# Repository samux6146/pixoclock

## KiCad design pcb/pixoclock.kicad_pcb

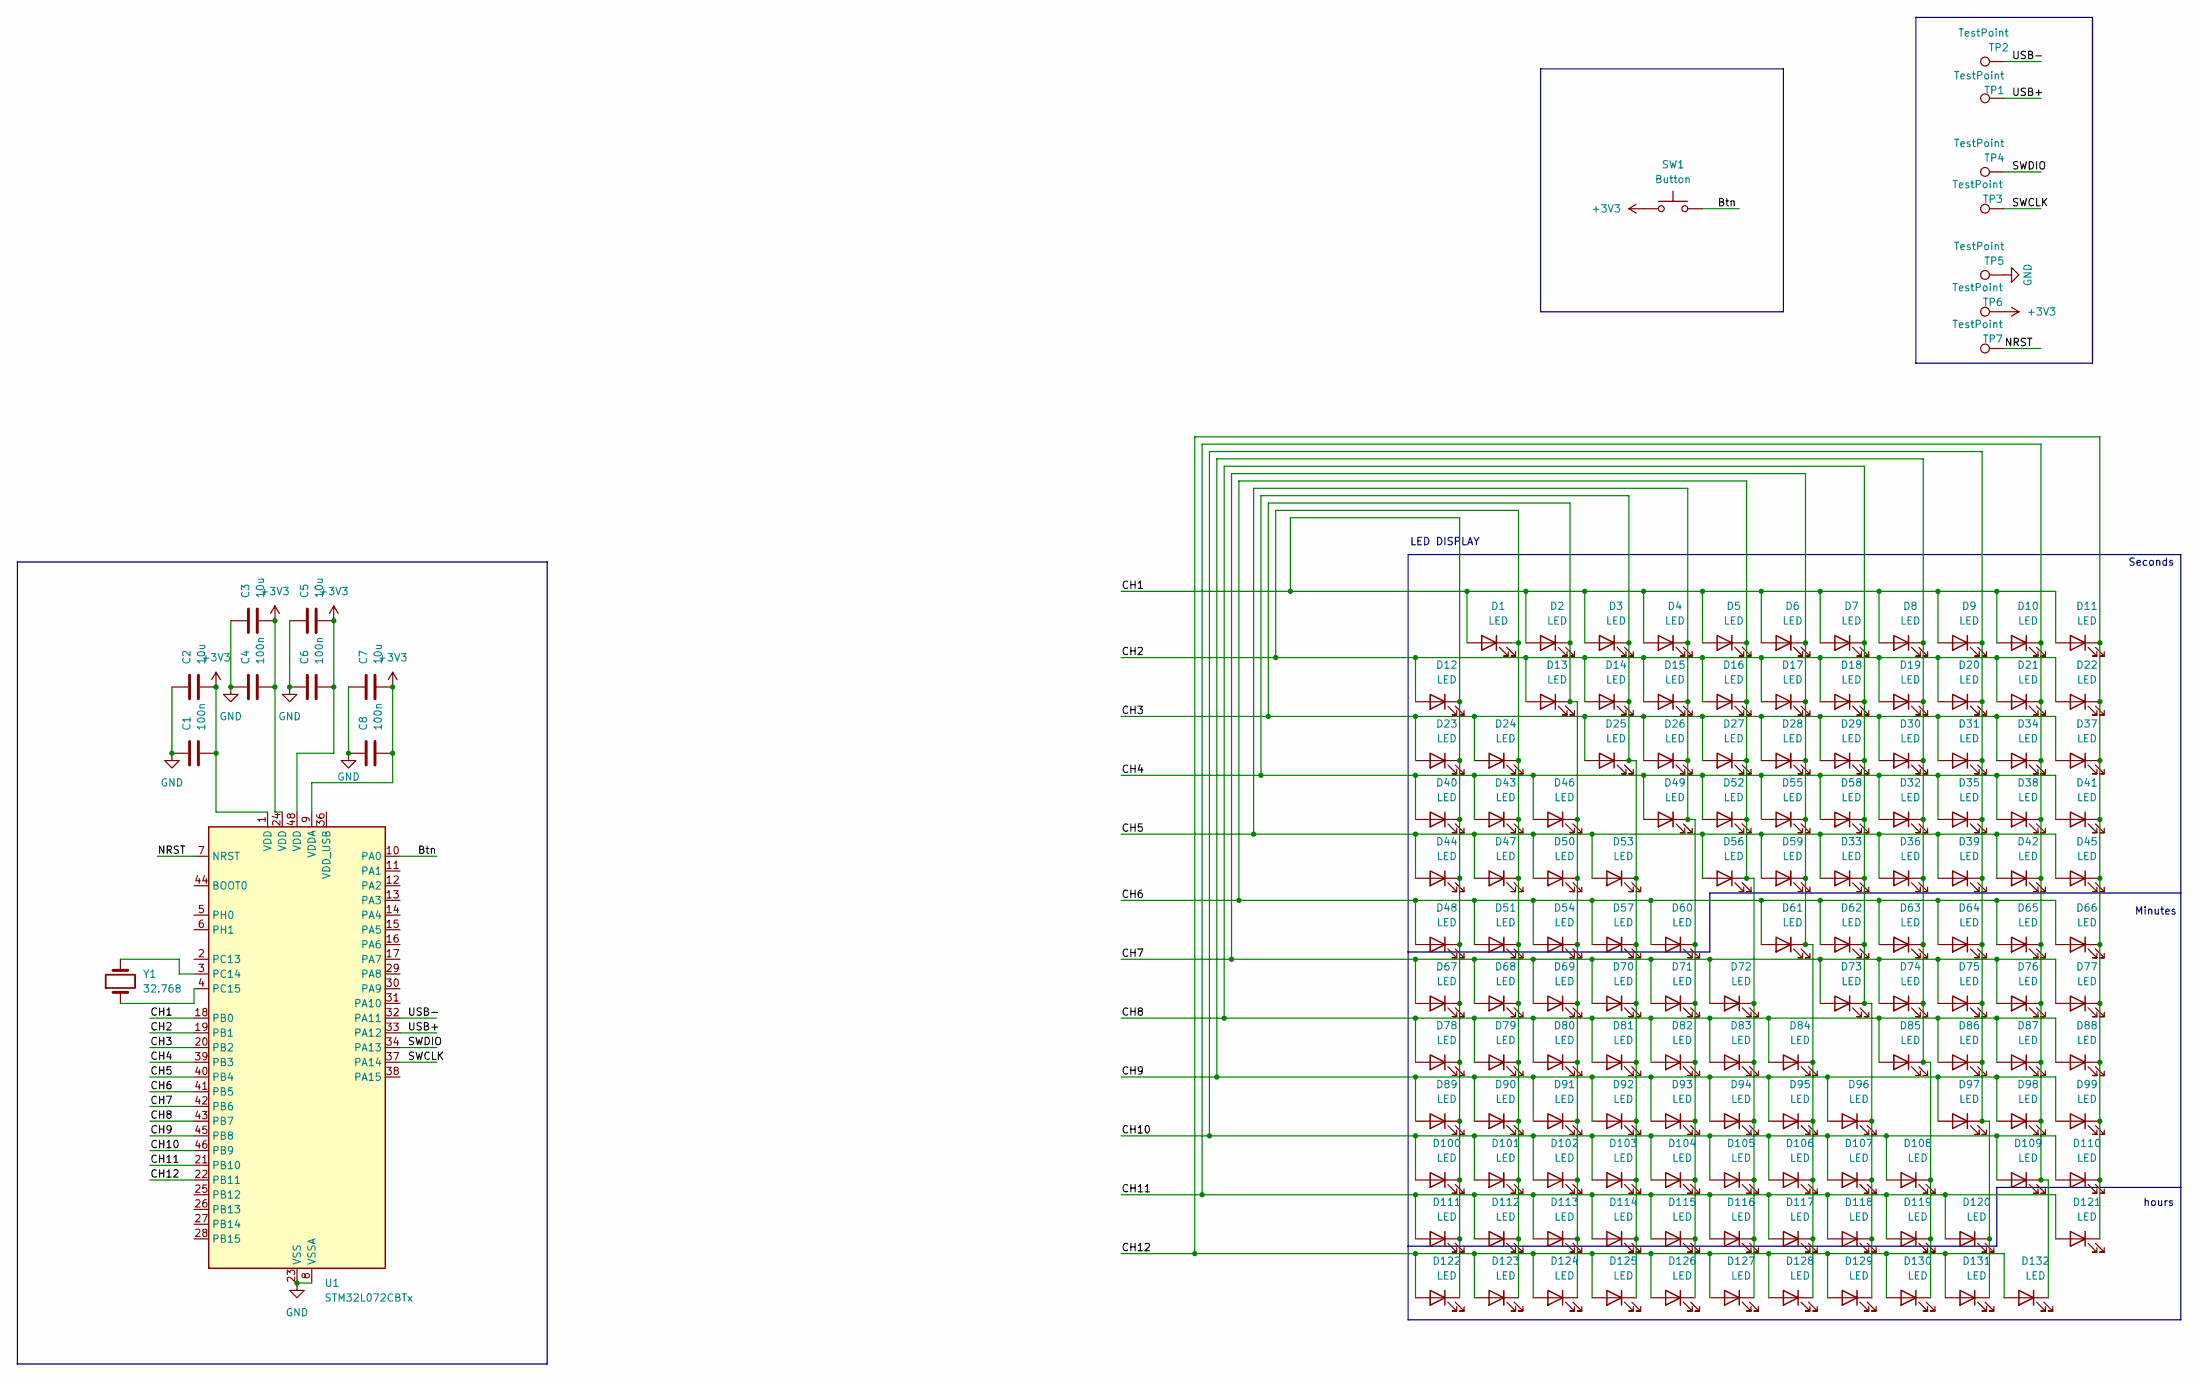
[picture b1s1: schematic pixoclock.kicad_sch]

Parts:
C1, C4, C6, C8: 100n; C_0402_1005Metric
C2, C3, C5, C7: 10u; C_0402_1005Metric
D1, D2, D3, D4, D5, D6, D7, D8, D9, D10, D11, D12, D13, D14, D15, D16, D17, D18, D19, D20, D21, D22, D23, D24, D25, D26, D27, D28, D29, D30, D31, D32, D33, D34, D35, D36, D37, D38, D39, D40, D41, D42, D43, D44, D45, D46, D47, D48, D49, D50, D51, D52, D53, D54, D55, D56, D57, D58, D59, D60, D61, D62, D63, D64, D65, D66, D67, D68, D69, D70, D71, D72, D73, D74, D75, D76, D77, D78, D79, D80, D81, D82, D83, D84, D85, D86, D87, D88, D89, D90, D91, D92, D93, D94, D95, D96, D97, D98, D99, D100, D101, D102, D103, D104, D105, D106, D107, D108, D109, D110, D111, D112, D113, D114, D115, D116, D117, D118, D119, D120, D121, D122, D123, D124, D125, D126, D127, D128, D129, D130, D131, D132: LED; LED_0201_0603Metric
SW1: Button; Panasonic_EVQPUJ_EVQPUA
TP1, TP2, TP3, TP4, TP5, TP6, TP7: TestPoint; TestPoint_Pad_D1.0mm
U1: STM32L072CBTx; LQFP-48_7x7mm_P0.5mm
Y1: 32.768; Crystal_SMD_3215-2Pin_3.2x1.5mm

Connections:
+3V3: C1.2, C2.2, C3.2, C4.2, C5.2, C6.2, C7.2, C8.2, SW1.1, TP6.1 (1_1), U1.1 (VDD), U1.9 (VDDA), U1.24 (VDD), U1.48 (VDD)
/Btn: SW1.2, U1.10 (PA0)
/CH1: D1.2 (A), D2.2 (A), D3.2 (A), D4.2 (A), D5.2 (A), D6.2 (A), D7.2 (A), D8.2 (A), D9.2 (A), D10.2 (A), D11.2 (A), D12.1 (K), D23.1 (K), D40.1 (K), D44.1 (K), D48.1 (K), D67.1 (K), D78.1 (K), D89.1 (K), D100.1 (K), D111.1 (K), D122.1 (K), U1.18 (PB0)
/CH2: D1.1 (K), D12.2 (A), D13.2 (A), D14.2 (A), D15.2 (A), D16.2 (A), D17.2 (A), D18.2 (A), D19.2 (A), D20.2 (A), D21.2 (A), D22.2 (A), D24.1 (K), D43.1 (K), D47.1 (K), D51.1 (K), D68.1 (K), D79.1 (K), D90.1 (K), D101.1 (K), D112.1 (K), D123.1 (K), U1.19 (PB1)
/CH3: D2.1 (K), D13.1 (K), D23.2 (A), D24.2 (A), D25.2 (A), D26.2 (A), D27.2 (A), D28.2 (A), D29.2 (A), D30.2 (A), D31.2 (A), D34.2 (A), D37.2 (A), D46.1 (K), D50.1 (K), D54.1 (K), D69.1 (K), D80.1 (K), D91.1 (K), D102.1 (K), D113.1 (K), D124.1 (K), U1.20 (PB2)
/CH4: D3.1 (K), D14.1 (K), D25.1 (K), D32.2 (A), D35.2 (A), D38.2 (A), D40.2 (A), D41.2 (A), D43.2 (A), D46.2 (A), D49.2 (A), D52.2 (A), D53.1 (K), D55.2 (A), D57.1 (K), D58.2 (A), D70.1 (K), D81.1 (K), D92.1 (K), D103.1 (K), D114.1 (K), D125.1 (K), U1.39 (PB3)
/CH5: D4.1 (K), D15.1 (K), D26.1 (K), D33.2 (A), D36.2 (A), D39.2 (A), D42.2 (A), D44.2 (A), D45.2 (A), D47.2 (A), D49.1 (K), D50.2 (A), D53.2 (A), D56.2 (A), D59.2 (A), D60.1 (K), D71.1 (K), D82.1 (K), D93.1 (K), D104.1 (K), D115.1 (K), D126.1 (K), U1.40 (PB4)
/CH6: D5.1 (K), D16.1 (K), D27.1 (K), D48.2 (A), D51.2 (A), D52.1 (K), D54.2 (A), D56.1 (K), D57.2 (A), D60.2 (A), D61.2 (A), D62.2 (A), D63.2 (A), D64.2 (A), D65.2 (A), D66.2 (A), D72.1 (K), D83.1 (K), D94.1 (K), D105.1 (K), D116.1 (K), D127.1 (K), U1.41 (PB5)
/CH7: D6.1 (K), D17.1 (K), D28.1 (K), D55.1 (K), D59.1 (K), D61.1 (K), D67.2 (A), D68.2 (A), D69.2 (A), D70.2 (A), D71.2 (A), D72.2 (A), D73.2 (A), D74.2 (A), D75.2 (A), D76.2 (A), D77.2 (A), D84.1 (K), D95.1 (K), D106.1 (K), D117.1 (K), D128.1 (K), U1.42 (PB6)
/CH8: D7.1 (K), D18.1 (K), D29.1 (K), D33.1 (K), D58.1 (K), D62.1 (K), D73.1 (K), D78.2 (A), D79.2 (A), D80.2 (A), D81.2 (A), D82.2 (A), D83.2 (A), D84.2 (A), D85.2 (A), D86.2 (A), D87.2 (A), D88.2 (A), D96.1 (K), D107.1 (K), D118.1 (K), D129.1 (K), U1.43 (PB7)
/CH9: D8.1 (K), D19.1 (K), D30.1 (K), D32.1 (K), D36.1 (K), D63.1 (K), D74.1 (K), D85.1 (K), D89.2 (A), D90.2 (A), D91.2 (A), D92.2 (A), D93.2 (A), D94.2 (A), D95.2 (A), D96.2 (A), D97.2 (A), D98.2 (A), D99.2 (A), D108.1 (K), D119.1 (K), D130.1 (K), U1.45 (PB8)
/CH10: D9.1 (K), D20.1 (K), D31.1 (K), D35.1 (K), D39.1 (K), D64.1 (K), D75.1 (K), D86.1 (K), D97.1 (K), D100.2 (A), D101.2 (A), D102.2 (A), D103.2 (A), D104.2 (A), D105.2 (A), D106.2 (A), D107.2 (A), D108.2 (A), D109.2 (A), D110.2 (A), D120.1 (K), D131.1 (K), U1.46 (PB9)
/CH11: D10.1 (K), D21.1 (K), D34.1 (K), D38.1 (K), D42.1 (K), D65.1 (K), D76.1 (K), D87.1 (K), D98.1 (K), D109.1 (K), D111.2 (A), D112.2 (A), D113.2 (A), D114.2 (A), D115.2 (A), D116.2 (A), D117.2 (A), D118.2 (A), D119.2 (A), D120.2 (A), D121.2 (A), D132.1 (K), U1.21 (PB10)
/CH12: D11.1 (K), D22.1 (K), D37.1 (K), D41.1 (K), D45.1 (K), D66.1 (K), D77.1 (K), D88.1 (K), D99.1 (K), D110.1 (K), D121.1 (K), D122.2 (A), D123.2 (A), D124.2 (A), D125.2 (A), D126.2 (A), D127.2 (A), D128.2 (A), D129.2 (A), D130.2 (A), D131.2 (A), D132.2 (A), U1.22 (PB11)
/NRST: TP7.1 (1_1), U1.7 (NRST)
/SWCLK: TP3.1 (1_1), U1.37 (PA14)
/SWDIO: TP4.1 (1_1), U1.34 (PA13)
/USB+: TP1.1 (1_1), U1.33 (PA12)
/USB-: TP2.1 (1_1), U1.32 (PA11)
GND: C1.1, C2.1, C3.1, C4.1, C5.1, C6.1, C7.1, C8.1, TP5.1 (1_1), U1.8 (VSSA), U1.23 (VSS), U1.35 (VSS), U1.47 (VSS)
unnamed: U1.3 (PC14), Y1.2
unnamed: U1.4 (PC15), Y1.1

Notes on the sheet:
Minutes
LED DISPLAY
hours
Seconds

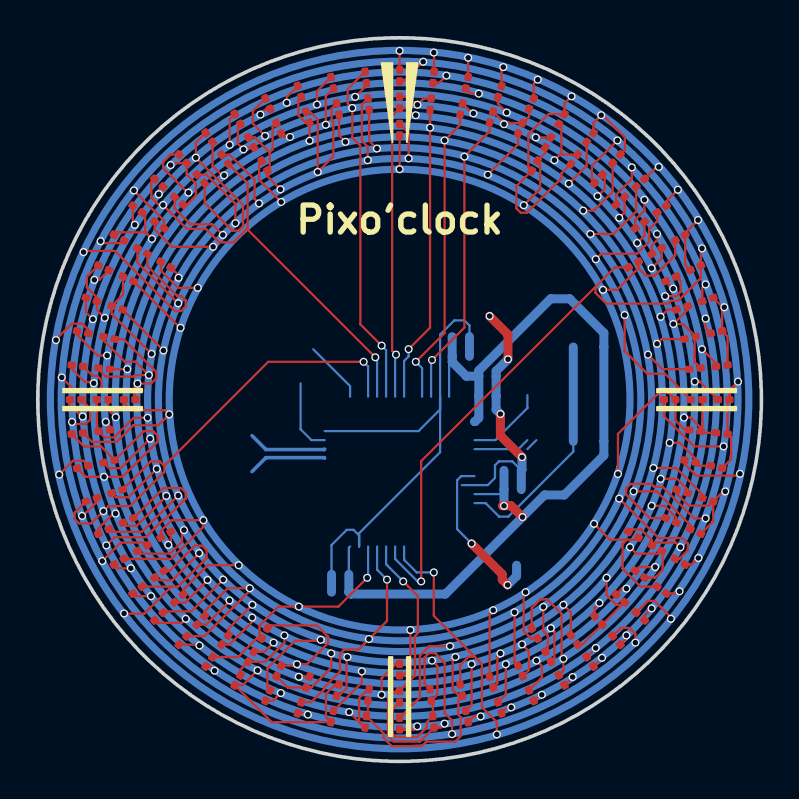
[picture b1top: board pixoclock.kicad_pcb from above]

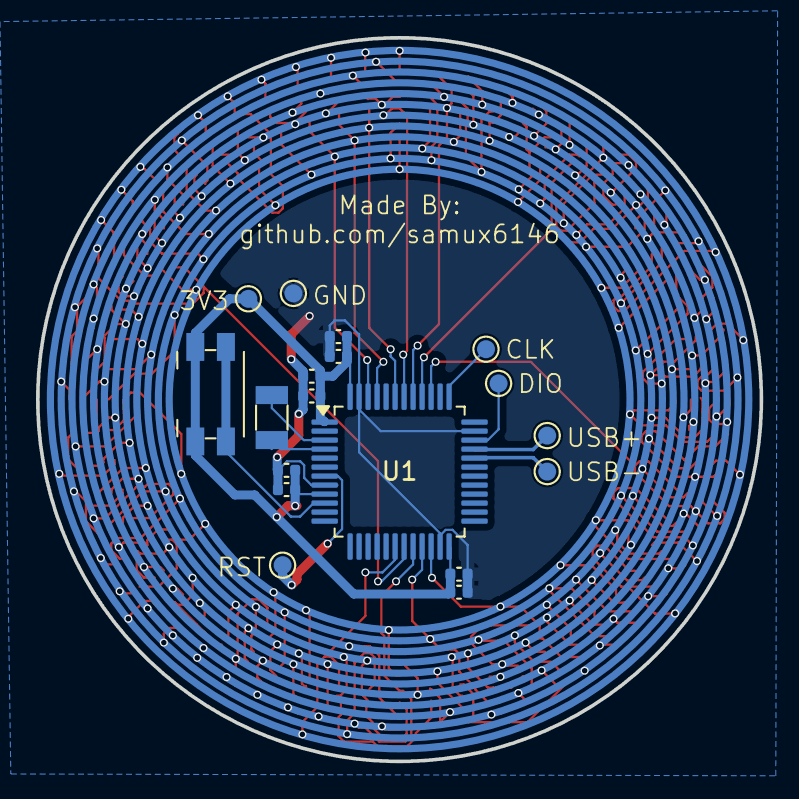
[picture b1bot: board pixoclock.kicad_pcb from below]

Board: 2 copper layers, 40.2 x 40.2 mm, 150 parts (18 on the bottom side), 22 nets.
